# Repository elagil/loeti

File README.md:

# Löti

Soldering station hardware and firmware, powered by USB PD, delivering up to 100 W.

Supports irons with thermocouples as temperature probes, for example
- JBC C210
- JBC C245

## Resources

- [Hardware design](./hardware)
- [Firmware](./firmware)

## Updating firmware

On the device, either
- hold the `BOOT`-button on the PCB and insert the USB cable into the data/debug port, or
- go to the user menu (long-press encoder button), scroll down to `DFU mode`, and select.

Once in DFU mode, flash a binary from the release artifacts. For example with

```bash
dfu-util -a 0 -s 0x08000000:leave -D <firmware_file_name>.bin
```

## The finished product

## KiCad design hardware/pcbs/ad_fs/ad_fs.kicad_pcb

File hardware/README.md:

# Hardware design

There are three PCBs that complete the build.

- The [main PCB](pcbs/main/),
- the [REAN TinyXLR adapter board](pcbs/adapter/), and
- a [holder for the acrylic display protection glass](pcbs/holder/).

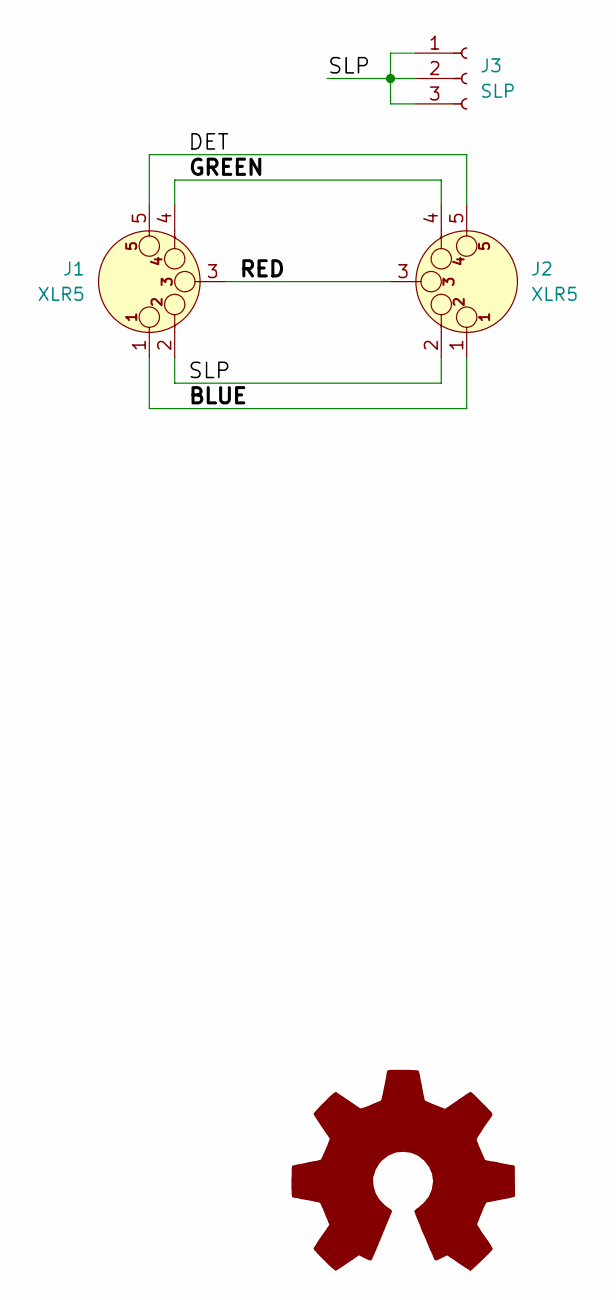
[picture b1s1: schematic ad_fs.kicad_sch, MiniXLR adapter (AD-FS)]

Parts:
J1, J2: XLR5; MiniXLR-5_Rean_RT5MPR
J3: SLP; PinSocket_1x03_P2.00mm_Vertical
oshw1: Logo_Open_Hardware_Large; OSHW-Symbol_6.7x6mm_SilkScreen

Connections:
/BLUE: J1.1, J2.1
/DET: J1.5, J2.5
/GREEN: J1.4 (P3), J2.4 (P3)
/RED: J1.3, J2.3
/SLP: J1.2, J2.2, J3.1, J3.2, J3.3

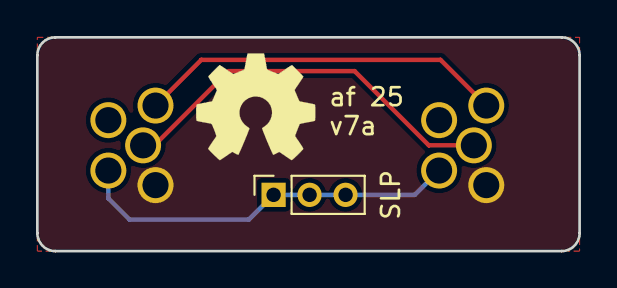
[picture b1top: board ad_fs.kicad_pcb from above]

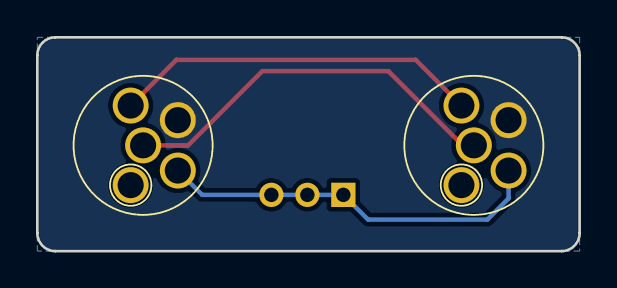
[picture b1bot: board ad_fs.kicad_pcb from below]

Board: 2 copper layers, 30.1 x 11.9 mm, 4 parts (2 on the bottom side), 5 nets.

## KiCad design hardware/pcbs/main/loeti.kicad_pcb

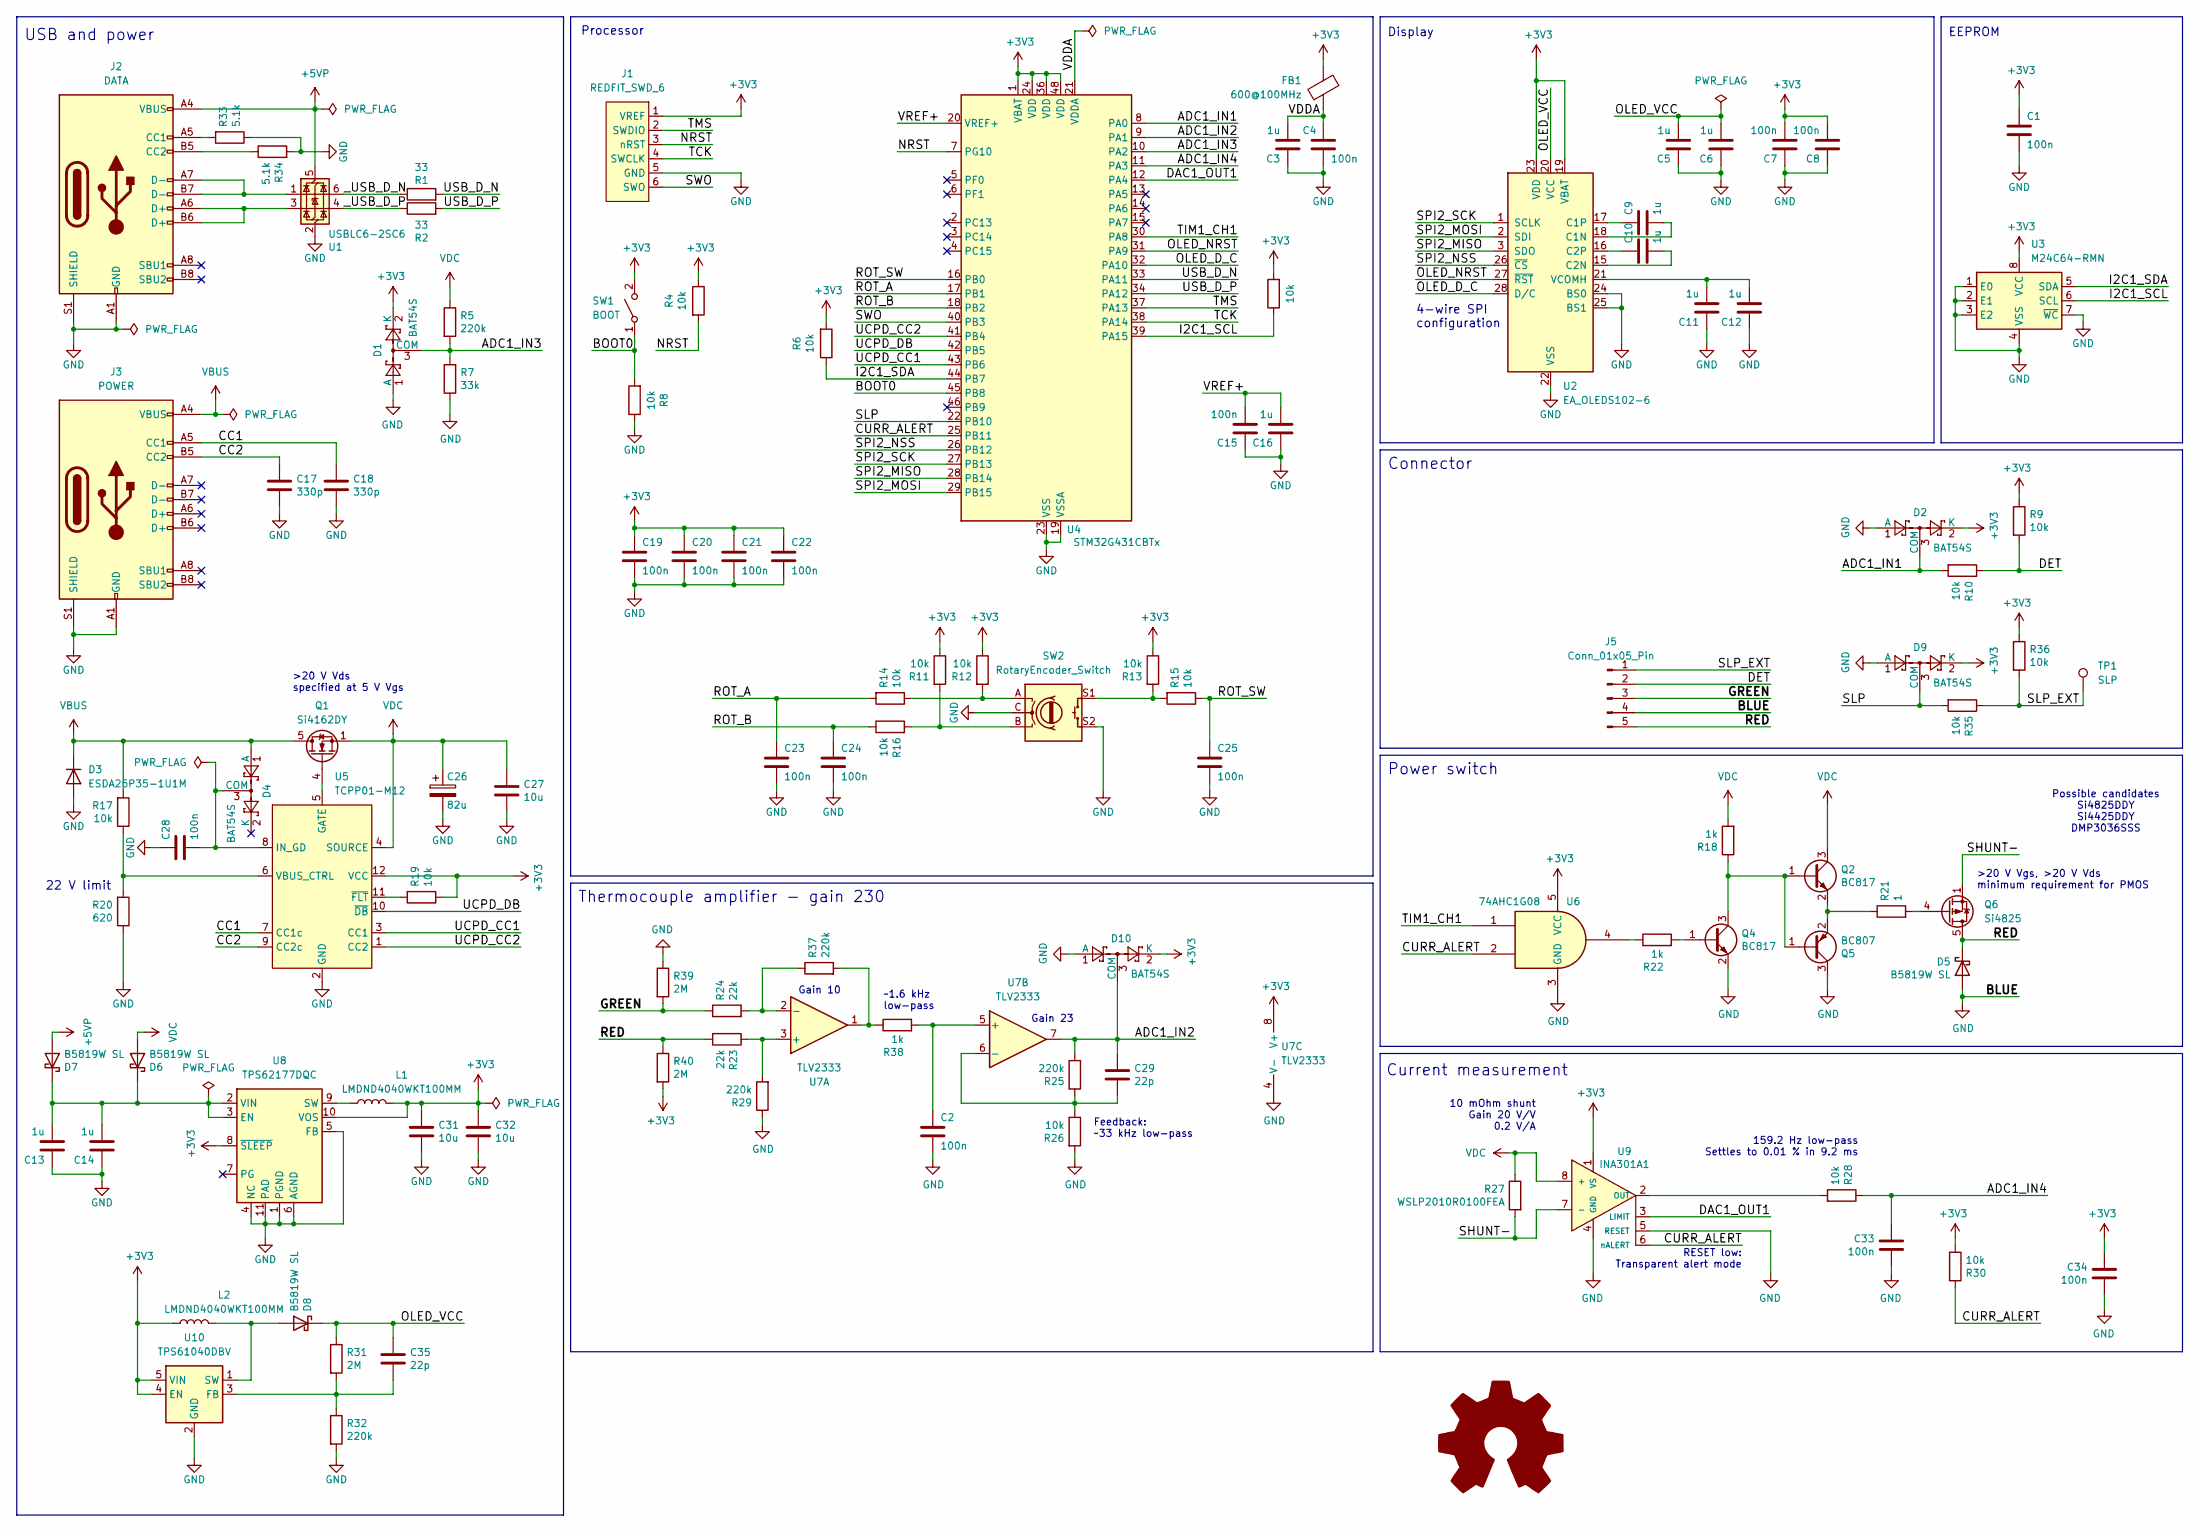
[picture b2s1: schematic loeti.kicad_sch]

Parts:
C1, C2, C4, C7, C8, C15, C19, C20, C21, C22, C23, C24, C25, C28, C33, C34: 100n; C_0603_1608Metric; MPN C14663
C3, C5, C6, C9, C10, C11, C12, C13, C14, C16: 1u; C_0603_1608Metric; MPN C15849
C17, C18: 330p; C_0603_1608Metric; MPN C1664
C26: 82u; CP_Radial_D8.0mm_P3.50mm
C27, C31, C32: 10u; C_1206_3216Metric; MPN C13585
C29, C35: 22p; C_0603_1608Metric; MPN C1653
D1, D2, D4, D9, D10: BAT54S; SOT-23; MPN C83935
D3: ESDA25P35-1U1M; ST_QFN-2L_1.6x1.0mm; MPN C1974707
D5, D6, D7, D8: B5819W SL; D_SOD-123; MPN C8598
FB1: 600@100MHz; L_0603_1608Metric; MPN C1002
J1: REDFIT_SWD_6; WR-WST REDFIT IDC 6 DBG
J2: DATA; USB_C_Receptacle_HRO_TYPE-C-31-M-12; MPN C165948
J3: POWER; USB_C_Receptacle_HRO_TYPE-C-31-M-12; MPN C165948
J5: Conn_01x05_Pin; PinHeader_1x05_P2.54mm_Horizontal
L1, L2: LMDND4040WKT100MM; L_Abracon_ASPI-0425
Q1: Si4162DY; SOIC-8_3.9x4.9mm_P1.27mm; MPN C727585
Q2, Q4: BC817; SOT-23; MPN C466643
Q5: BC807; SOT-23; MPN C466642
Q6: Si4825; SOIC-8_3.9x4.9mm_P1.27mm; MPN C3289788
R1, R2: 33; R_0603_1608Metric; MPN C23140
R3, R4, R6, R8, R9, R10, R11, R12, R13, R14, R15, R16, R17, R19, R26, R28, R30, R35, R36: 10k; R_0603_1608Metric; MPN C25804
R5, R25, R29, R32, R37: 220k; R_0603_1608Metric; MPN C22961
R7: 33k; R_0603_1608Metric; MPN C4216
R18, R22, R38: 1k; R_0603_1608Metric; MPN C21190
R20: 620; R_0603_1608Metric
R21: 1; R_0603_1608Metric; MPN C22936
R23, R24: 22k; R_0603_1608Metric; MPN C31850
R27: WSLP2010R0100FEA; R_2010_5025Metric; MPN C844087
R31, R39, R40: 2M; R_0603_1608Metric; MPN C22976
R33, R34: 5.1k; R_0603_1608Metric; MPN C23186
SW1: BOOT; SW_SPST_TL3342; MPN C318884
SW2: RotaryEncoder_Switch; RotaryEncoder_Bourns_Horizontal_PEC09-2xxxF-Sxxxx
TP1: SLP; TestPoint_Plated_Hole_D2.0mm
U1: USBLC6-2SC6; SOT-23-6; MPN C7519; JLCPCB Rotation Offset 180
U2: EA_OLEDS102-6
U3: M24C64-RMN; SOIC-8_3.9x4.9mm_P1.27mm; MPN C79988; JLCPCB Rotation Offset -90
U4: STM32G431CBTx; LQFP-48_7x7mm_P0.5mm; MPN C529355
U5: TCPP01-M12; QFN-12-1EP_3x3mm_P0.51mm_EP1.45x1.45mm; MPN C1121848
U6: 74AHC1G08; SOT-353_SC-70-5; MPN C459531
U7: TLV2333; SOIC-8_3.9x4.9mm_P1.27mm; MPN C176649
U8: TPS62177DQC; WSON-10-1EP_2x3mm_P0.5mm_EP0.84x2.4mm_ThermalVias; MPN C91241
U9: INA301A1; VSSOP-8_3x3mm_P0.65mm; MPN C471062
U10: TPS61040DBV; SOT-23-5
oshw1: Logo_Open_Hardware_Large; OSHW-Symbol_6.7x6mm_SilkScreen

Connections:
+3V3: C1.1, C7.2, C8.2, C19.1, C20.1, C21.1, C22.1, C31.1, C32.1, C34.1, D1.2 (K), D2.2 (K), D9.2 (K), D10.2 (K), FB1.1, J1.1 (VREF), L1.2, L2.1, R3.2, R4.1, R6.2, R9.1, R11.1, R12.1, R13.1, R19.1, R30.2, R36.1, R40.2, SW1.2 (B), U2.19 (VBAT), U2.23 (VDD), U3.8 (VCC), U4.1 (VBAT), U4.24 (VDD), U4.36 (VDD), U4.48 (VDD), U5.12 (VCC), U6.5 (VCC), U7.8 (V+), U8.8 (~SLEEP), U8.10 (VOS), U9.1 (VS), U10.4 (EN), U10.5 (VIN)
+5VP: D7.2 (A), J2.A4 (VBUS), J2.A9 (VBUS), J2.B4 (VBUS), J2.B9 (VBUS), U1.5 (VBUS)
/ADC1_IN1: D2.3 (COM), R10.2, U4.8 (PA0)
/ADC1_IN2: C29.1, D10.3 (COM), R25.2, U4.9 (PA1), U7.7
/ADC1_IN3: D1.3 (COM), R5.2, R7.2, U4.10 (PA2)
/ADC1_IN4: C33.1, R28.1, U4.11 (PA3)
/BOOT0: R8.2, SW1.1 (A), U4.45 (PB8)
/CC1: C18.1, J3.A5 (CC1), U5.7 (CC1c)
/CC2: C17.1, J3.B5 (CC2), U5.9 (CC2c)
/CURR_ALERT: R30.1, U4.25 (PB11), U6.2, U9.6 (nALERT)
/DAC1_OUT1: U4.12 (PA4), U9.3 (LIMIT)
/DET: J5.2, R9.2, R10.1
/GREEN: J5.3, R24.1, R39.2
/I2C1_SCL: R3.1, U3.6 (SCL), U4.39 (PA15)
/I2C1_SDA: R6.1, U3.5 (SDA), U4.44 (PB7)
/NRST: J1.3 (nRST), R4.2, U4.7 (PG10)
/OLED_D_C: U2.28 (D/C), U4.32 (PA10)
/OLED_NRST: U2.27 (~RST), U4.31 (PA9)
/OLED_VCC: C5.2, C6.2, C35.1, D8.1 (K), R31.1, U2.20 (VCC)
/RED: D5.1 (K), J5.5, Q6.5 (D), Q6.6 (D), Q6.7 (D), Q6.8 (D), R23.2, R40.1
/ROT_A: C23.1, R14.2, U4.17 (PB1)
/ROT_B: C24.1, R16.1, U4.18 (PB2)
/ROT_SW: C25.1, R15.1, U4.16 (PB0)
/SHUNT-: Q6.1 (S), Q6.2 (S), Q6.3 (S), R27.2, U9.7 (-)
/SLP: D9.3 (COM), R35.2, U4.22 (PB10)
/SLP_EXT: J5.1, R35.1, R36.2, TP1.1
/SPI2_MISO: U2.3 (SDO), U4.28 (PB14)
/SPI2_MOSI: U2.2 (SDI), U4.29 (PB15)
/SPI2_NSS: U2.26 (~CS), U4.26 (PB12)
/SPI2_SCK: U2.1 (SCLK), U4.27 (PB13)
/SWO: J1.6 (SWO), U4.40 (PB3)
/TCK: J1.4 (SWCLK), U4.38 (PA14)
/TIM1_CH1: U4.30 (PA8), U6.1
/TMS: J1.2 (SWDIO), U4.37 (PA13)
/UCPD_CC1: U4.43 (PB6), U5.3 (CC1)
/UCPD_CC2: U4.41 (PB4), U5.1 (CC2)
/UCPD_DB: U4.42 (PB5), U5.10 (~DB)
/USB_D_N: R1.2, U4.33 (PA11)
/USB_D_P: R2.2, U4.34 (PA12)
/VDDA: C3.2, C4.1, FB1.2, U4.21 (VDDA)
/VREF+: C15.2, C16.2, U4.20 (VREF+)
/_USB_D_N: R1.1, U1.6 (I/O1)
/_USB_D_P: R2.1, U1.4 (I/O2)
GND: C1.2, C2.2, C3.1, C4.2, C5.1, C6.1, C7.1, C8.1, C11.1, C12.1, C13.1, C14.1, C15.1, C16.1, C17.2, C18.2, C19.2, C20.2, C21.2, C22.2, C23.2, C24.2, C25.2, C26.2, C27.2, C28.1, C31.2, C32.2, C33.2, C34.2, D1.1 (A), D2.1 (A), D3.2 (A), D5.2 (A), D9.1 (A), D10.1 (A), J1.5 (GND), J2.A1 (GND), J2.A12 (GND), J2.B1 (GND), J2.B12 (GND), J2.S1 (SHIELD), J3.A1 (GND), J3.A12 (GND), J3.B1 (GND), J3.B12 (GND), J3.S1 (SHIELD), J5.4, Q4.2 (E), Q5.3 (C), R7.1, R8.1, R20.1, R26.2, R29.1, R32.2, R33.1, R34.2, R39.1, SW2.C, SW2.S2, U1.2 (GND), U2.22 (VSS), U2.24 (BS0), U2.25 (BS1), U3.1 (E0), U3.2 (E1), U3.3 (E2), U3.4 (VSS), U3.7 (~WC), U4.19 (VSSA), U4.23 (VSS), U4.35 (VSS), U4.47 (VSS), U5.2 (GND), U5.13 (GND), U6.3 (GND), U7.4 (V-), U8.1 (PGND), U8.4 (NC), U8.5 (FB), U8.6 (AGND), U8.11 (PAD), U9.4 (GND), U9.5 (RESET), U10.2 (GND)
unnamed: C28.2, D4.3 (COM), U5.8 (IN_GD)
unnamed: C13.2, C14.2, D6.1 (K), D7.1 (K), U8.2 (VIN), U8.3 (EN)
unnamed: D8.2 (A), L2.2, U10.1 (SW)
unnamed: J2.A5 (CC1), R33.2
unnamed: J2.B5 (CC2), R34.1
unnamed: J2.A6 (D+), J2.B6 (D+), U1.3 (I/O2)
unnamed: J2.A7 (D-), J2.B7 (D-), U1.1 (I/O1)
unnamed: Q1.4 (G), U5.5 (GATE)
unnamed: Q2.1 (B), Q4.3 (C), Q5.1 (B), R18.1
unnamed: Q2.2 (E), Q5.2 (E), R21.1
unnamed: Q4.1 (B), R22.2
unnamed: Q6.4 (G), R21.2
unnamed: R11.2, R16.2, SW2.B
unnamed: R12.2, R14.1, SW2.A
unnamed: R13.2, R15.2, SW2.S1
unnamed: R22.1, U6.4
unnamed: R37.2, R38.1, U7.1
unnamed: C9.2, U2.18 (C1N)
unnamed: C9.1, U2.17 (C1P)
unnamed: C10.2, U2.15 (C2N)
unnamed: C10.1, U2.16 (C2P)
unnamed: C11.2, C12.2, U2.21 (VCOMH)
unnamed: R17.1, R20.2, U5.6 (VBUS_CTRL)
unnamed: R19.2, U5.11 (~FLT)
unnamed: R23.1, R29.2, U7.3 (+)
unnamed: R24.2, R37.1, U7.2 (-)
unnamed: C2.1, R38.2, U7.5 (+)
unnamed: C29.2, R25.1, R26.1, U7.6 (-)
unnamed: L1.1, U8.9 (SW)
unnamed: R28.2, U9.2 (OUT)
unnamed: C35.2, R31.2, R32.1, U10.3 (FB)
VBUS: D3.1 (K), D4.1 (A), J3.A4 (VBUS), J3.A9 (VBUS), J3.B4 (VBUS), J3.B9 (VBUS), Q1.5 (D), Q1.6 (D), Q1.7 (D), Q1.8 (D), R17.2
VDC: C26.1, C27.1, D6.2 (A), Q1.1 (S), Q1.2 (S), Q1.3 (S), Q2.3 (C), R5.1, R18.2, R27.1, U5.4 (SOURCE), U9.8 (+)

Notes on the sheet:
~1.6 kHz low-pass
>20 V Vgs, >20 V Vds minimum requirement for PMOS
USB and power
22 V limit
>20 V Vds specified at 5 V Vgs
159.2 Hz low-pass Settles to 0.01 % in 9.2 ms
RESET low: Transparent alert mode
Connector
EEPROM
Possible candidates Si4825DDY Si4425DDY DMP3036SSS
Gain 23
Gain 10
Feedback: ~33 kHz low-pass
Thermocouple amplifier - gain 230
Power switch
4-wire SPI configuration
Display
Processor
10 mOhm shunt Gain 20 V/V 0.2 V/A
Current measurement

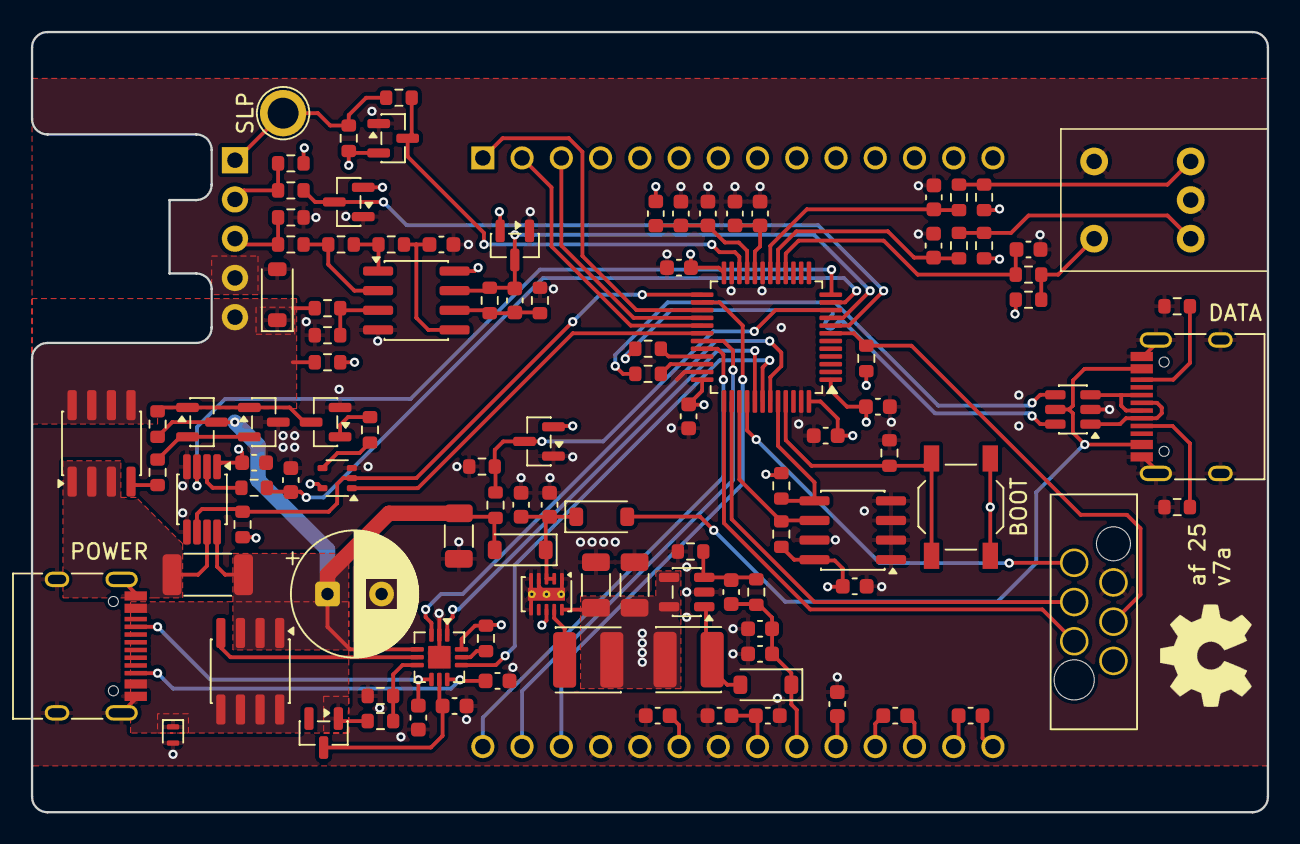
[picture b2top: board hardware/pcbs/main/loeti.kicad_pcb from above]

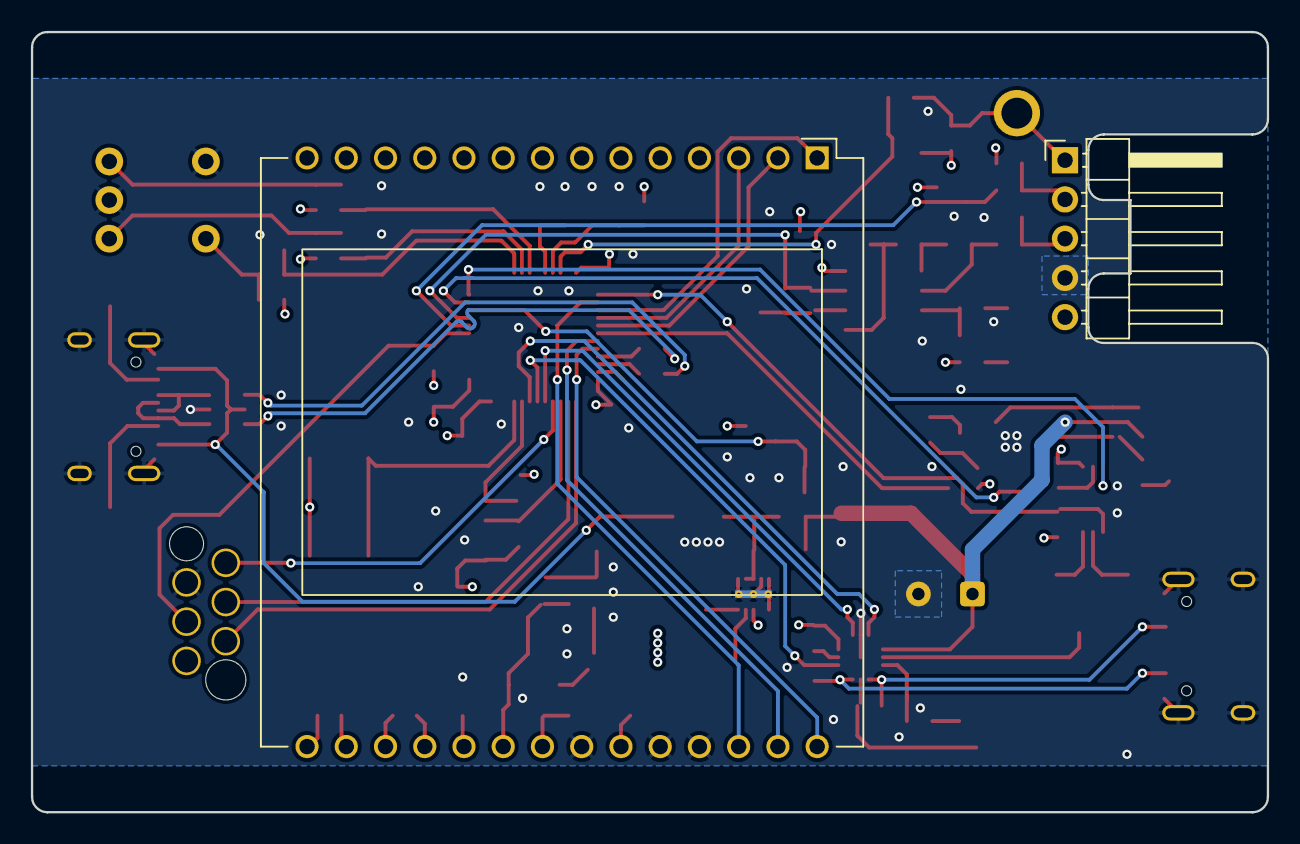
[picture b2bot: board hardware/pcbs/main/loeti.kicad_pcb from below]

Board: 4 copper layers, 80.0 x 50.5 mm, 110 parts (2 on the bottom side), 77 nets.

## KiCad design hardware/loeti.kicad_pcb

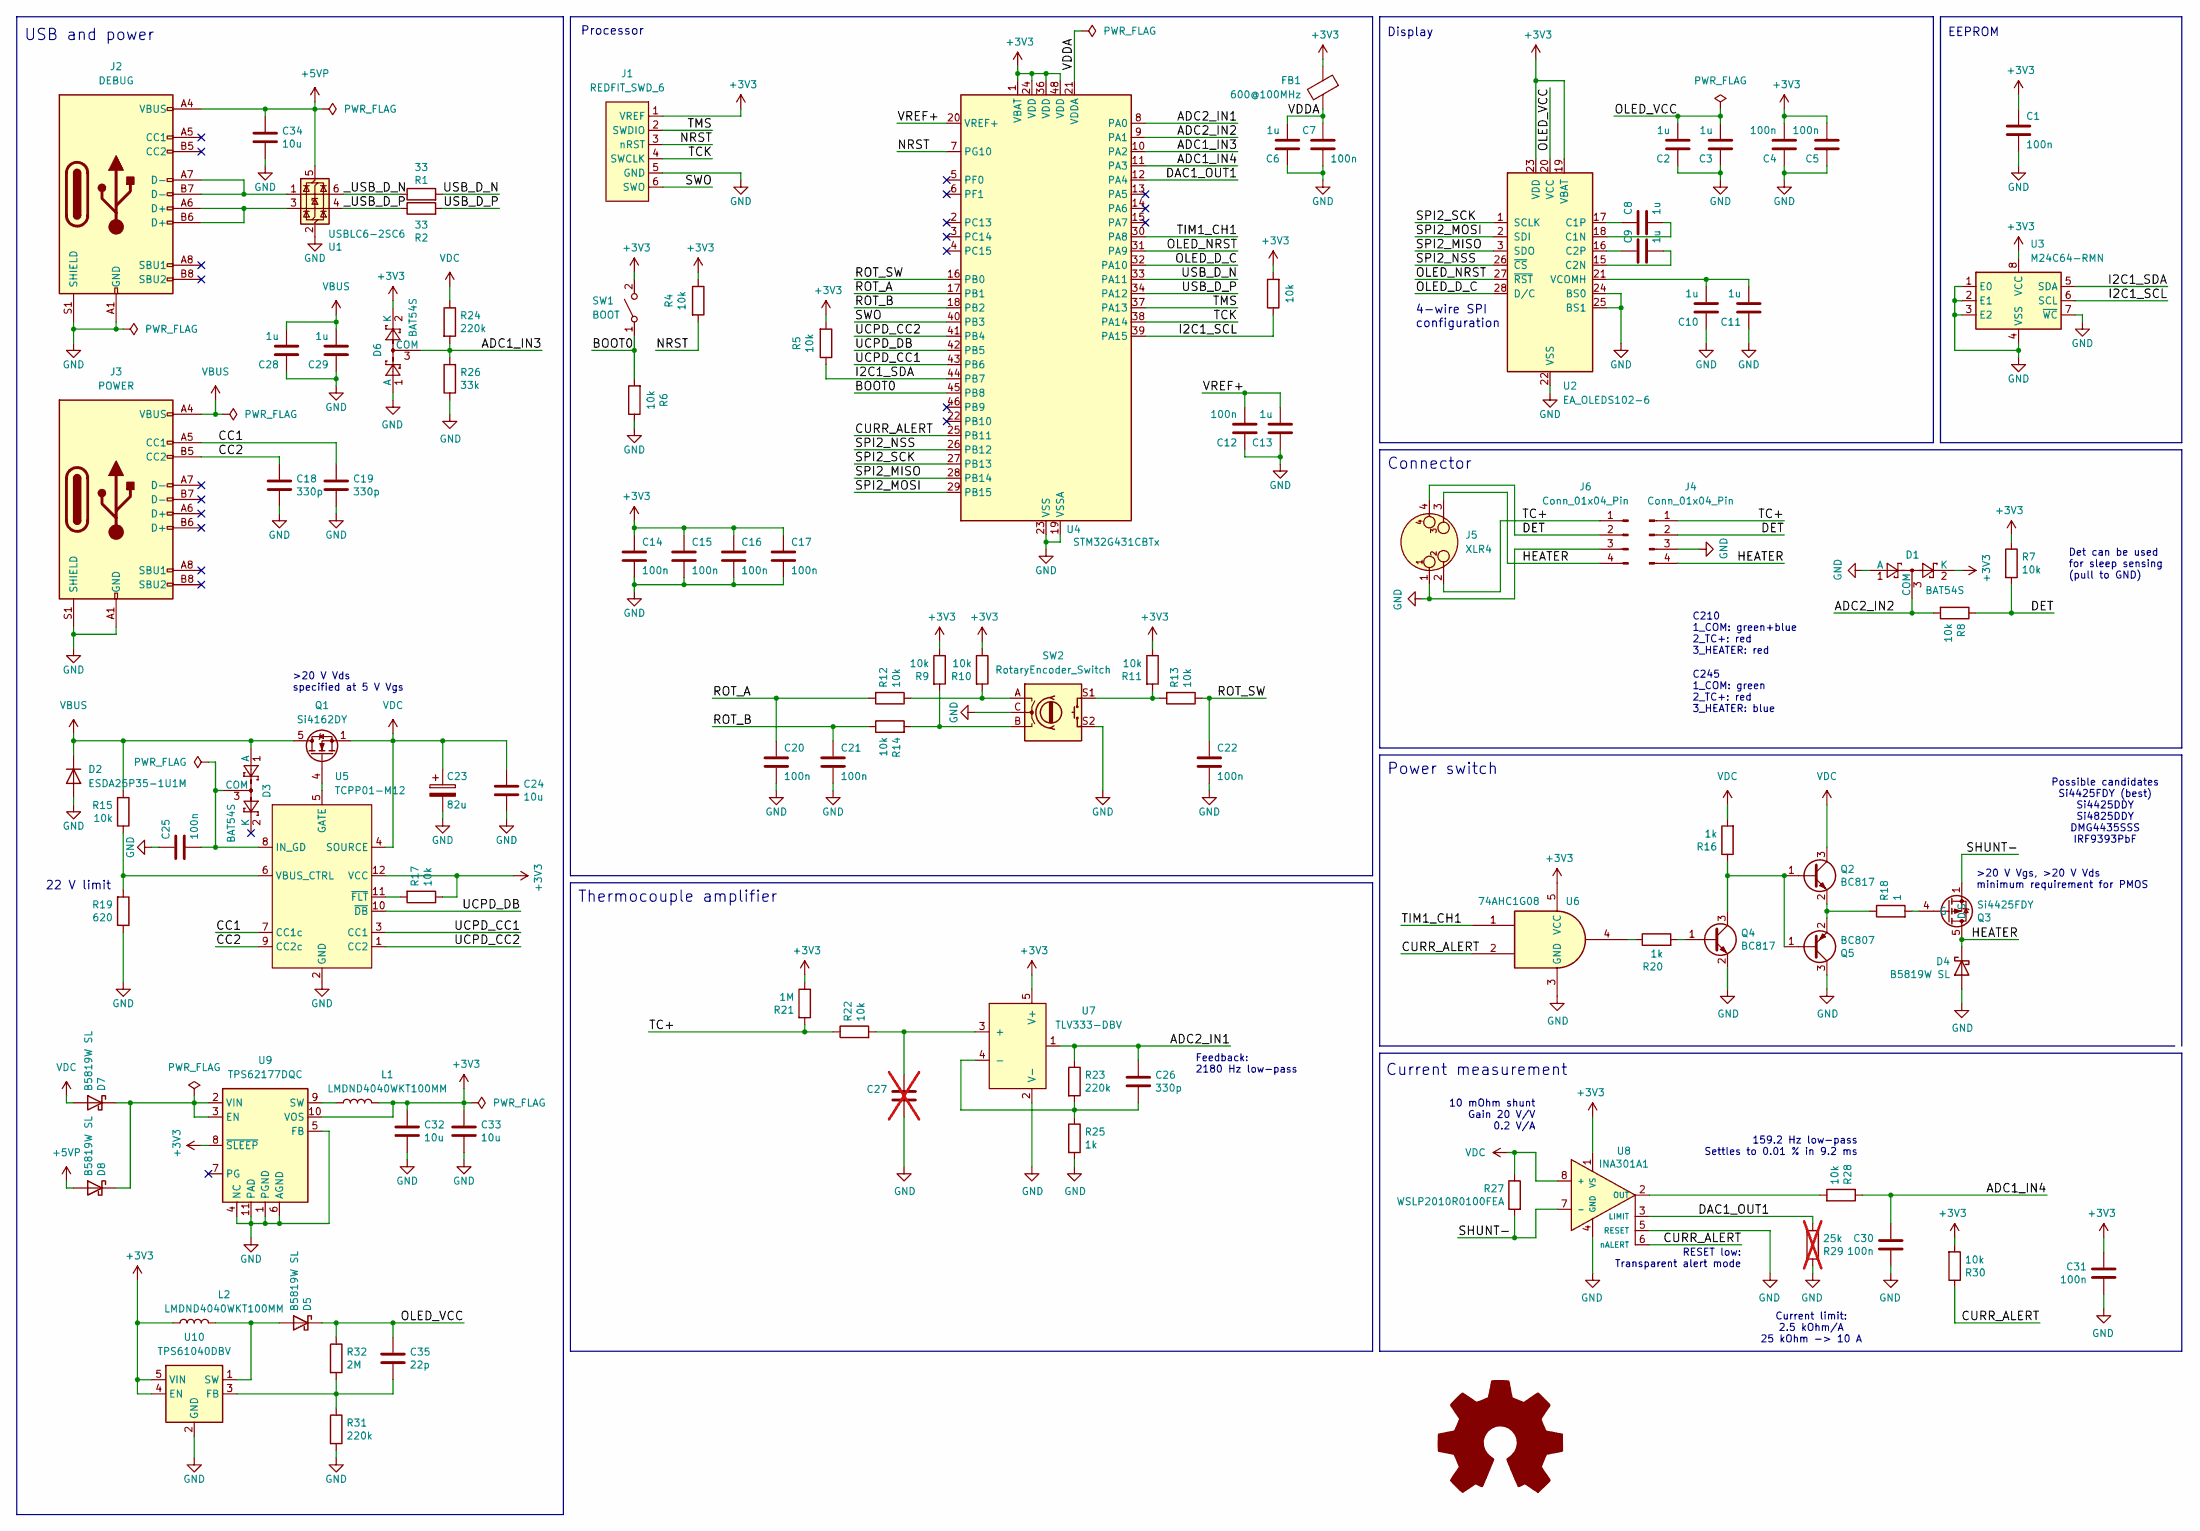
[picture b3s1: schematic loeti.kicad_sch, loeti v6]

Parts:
C1, C4, C5, C7, C12, C14, C15, C16, C17, C20, C21, C22, C25, C30, C31: 100n; C_0603_1608Metric; MPN C14663
C2, C3, C6, C8, C9, C10, C11, C13, C28, C29: 1u; C_0603_1608Metric; MPN C15849
C18, C19, C26: 330p; C_0603_1608Metric; MPN C1664
C23: 82u; CP_Radial_D10.0mm_P3.50mm
C24, C32, C33, C34: 10u; C_1206_3216Metric; MPN C13585
C27: C_0603_1608Metric; not fitted
C35: 22p; C_0603_1608Metric; MPN C1664
D1, D3, D6: BAT54S; SOT-23; MPN C83935
D2: ESDA25P35-1U1M; ST_QFN-2L_1.6x1.0mm; MPN C1974707
D4, D5, D7, D8: B5819W SL; D_SOD-123; MPN C8598
FB1: 600@100MHz; L_0603_1608Metric; MPN C1002
J1: REDFIT_SWD_6; WR-WST REDFIT IDC 6 DBG
J2: DEBUG; USB_C_Receptacle_HRO_TYPE-C-31-M-12; MPN C165948
J3: POWER; USB_C_Receptacle_HRO_TYPE-C-31-M-12; MPN C165948
J4: Conn_01x04_Pin; PinHeader_1x04_P2.54mm_Horizontal
J5: XLR4; MiniXLR-4_Rean_RT4MPR
J6: Conn_01x04_Pin; PinHeader_1x04_P2.54mm_Vertical
L1, L2: LMDND4040WKT100MM; L_Abracon_ASPI-0425
Q1: Si4162DY; SOIC-8_3.9x4.9mm_P1.27mm; MPN C727585
Q2, Q4: BC817; SOT-23; MPN C466643
Q3: Si4425FDY; SO-8_3.9x4.9mm_P1.27mm; MPN C3289788
Q5: BC807; SOT-23; MPN C466642
R1, R2: 33; R_0603_1608Metric; MPN C23140
R3, R4, R5, R6, R7, R8, R9, R10, R11, R12, R13, R14, R15, R17, R22, R28, R30: 10k; R_0603_1608Metric; MPN C25804
R16, R20, R25: 1k; R_0603_1608Metric; MPN C21190
R18: 1; R_0603_1608Metric; MPN C22936
R19: 620; R_0603_1608Metric
R21: 1M; R_0603_1608Metric; MPN C22935
R23, R24, R31: 220k; R_0603_1608Metric; MPN C22961
R26: 33k; R_0603_1608Metric; MPN C4216
R27: WSLP2010R0100FEA; R_2010_5025Metric; MPN C844087
R29: 25k; R_0603_1608Metric; not fitted
R32: 2M; R_0603_1608Metric; MPN C22961
SW1: BOOT; SW_SPST_TL3342; MPN C318884
SW2: RotaryEncoder_Switch; RotaryEncoder_Bourns_Horizontal_PEC09-2xxxF-Sxxxx
U1: USBLC6-2SC6; SOT-23-6; MPN C7519; JLCPCB Rotation Offset 180
U2: EA_OLEDS102-6
U3: M24C64-RMN; SOIC-8_3.9x4.9mm_P1.27mm; MPN C79988; JLCPCB Rotation Offset -90
U4: STM32G431CBTx; LQFP-48_7x7mm_P0.5mm; MPN C529355
U5: TCPP01-M12; QFN-12-1EP_3x3mm_P0.51mm_EP1.45x1.45mm; MPN C1121848
U6: 74AHC1G08; SOT-353_SC-70-5; MPN C459531
U7: TLV333-DBV; SOT-23-5; MPN C75209
U8: INA301A1; VSSOP-8_3x3mm_P0.65mm; MPN C471062
U9: TPS62177DQC; WSON-10-1EP_2x3mm_P0.5mm_EP0.84x2.4mm_ThermalVias; MPN C91241
U10: TPS61040DBV; SOT-23-5
oshw1: Logo_Open_Hardware_Large; OSHW-Symbol_6.7x6mm_SilkScreen

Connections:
+3V3: C1.1, C4.2, C5.2, C14.1, C15.1, C16.1, C17.1, C31.1, C32.1, C33.1, D1.2 (K), D6.2 (K), FB1.1, J1.1 (VREF), L1.2, L2.1, R3.2, R4.1, R5.2, R7.1, R9.1, R10.1, R11.1, R17.1, R21.1, R30.2, SW1.2 (B), U2.19 (VBAT), U2.23 (VDD), U3.8 (VCC), U4.1 (VBAT), U4.24 (VDD), U4.36 (VDD), U4.48 (VDD), U5.12 (VCC), U6.5 (VCC), U7.5 (V+), U8.1 (VS), U9.8 (~SLEEP), U9.10 (VOS), U10.4 (EN), U10.5 (VIN)
+5VP: C34.1, D8.2 (A), J2.A4 (VBUS), J2.A9 (VBUS), J2.B4 (VBUS), J2.B9 (VBUS), U1.5 (VBUS)
/ADC1_IN3: D6.3 (COM), R24.2, R26.2, U4.10 (PA2)
/ADC1_IN4: C30.1, R28.1, U4.11 (PA3)
/ADC2_IN1: C26.1, R23.1, U4.8 (PA0), U7.1
/ADC2_IN2: D1.3 (COM), R8.2, U4.9 (PA1)
/BOOT0: R6.2, SW1.1 (A), U4.45 (PB8)
/CC1: C19.1, J3.A5 (CC1), U5.7 (CC1c)
/CC2: C18.1, J3.B5 (CC2), U5.9 (CC2c)
/CURR_ALERT: R30.1, U4.25 (PB11), U6.2, U8.6 (nALERT)
/DAC1_OUT1: R29.2, U4.12 (PA4), U8.3 (LIMIT)
/DET: J4.2, J5.4, J6.2, R7.2, R8.1
/HEATER: D4.1 (K), J4.4, J5.3, J6.4, Q3.5 (D), Q3.6 (D), Q3.7 (D), Q3.8 (D)
/I2C1_SCL: R3.1, U3.6 (SCL), U4.39 (PA15)
/I2C1_SDA: R5.1, U3.5 (SDA), U4.44 (PB7)
/NRST: J1.3 (nRST), R4.2, U4.7 (PG10)
/OLED_D_C: U2.28 (D/C), U4.32 (PA10)
/OLED_NRST: U2.27 (~RST), U4.31 (PA9)
/OLED_VCC: C2.2, C3.2, C35.1, D5.1 (K), R32.1, U2.20 (VCC)
/ROT_A: C20.1, R12.2, U4.17 (PB1)
/ROT_B: C21.1, R14.1, U4.18 (PB2)
/ROT_SW: C22.1, R13.1, U4.16 (PB0)
/SHUNT-: Q3.1 (S), Q3.2 (S), Q3.3 (S), R27.2, U8.7 (-)
/SPI2_MISO: U2.3 (SDO), U4.28 (PB14)
/SPI2_MOSI: U2.2 (SDI), U4.29 (PB15)
/SPI2_NSS: U2.26 (~CS), U4.26 (PB12)
/SPI2_SCK: U2.1 (SCLK), U4.27 (PB13)
/SWO: J1.6 (SWO), U4.40 (PB3)
/TC+: J4.1, J5.2, J6.1, R21.2, R22.1
/TCK: J1.4 (SWCLK), U4.38 (PA14)
/TIM1_CH1: U4.30 (PA8), U6.1
/TMS: J1.2 (SWDIO), U4.37 (PA13)
/UCPD_CC1: U4.43 (PB6), U5.3 (CC1)
/UCPD_CC2: U4.41 (PB4), U5.1 (CC2)
/UCPD_DB: U4.42 (PB5), U5.10 (~DB)
/USB_D_N: R1.2, U4.33 (PA11)
/USB_D_P: R2.2, U4.34 (PA12)
/VDDA: C6.2, C7.1, FB1.2, U4.21 (VDDA)
/VREF+: C12.2, C13.2, U4.20 (VREF+)
/_USB_D_N: R1.1, U1.6 (I/O1)
/_USB_D_P: R2.1, U1.4 (I/O2)
GND: C1.2, C2.1, C3.1, C4.1, C5.1, C6.1, C7.2, C10.1, C11.1, C12.1, C13.1, C14.2, C15.2, C16.2, C17.2, C18.2, C19.2, C20.2, C21.2, C22.2, C23.2, C24.2, C25.1, C27.2, C28.1, C29.1, C30.2, C31.2, C32.2, C33.2, C34.2, D1.1 (A), D2.2 (A), D4.2 (A), D6.1 (A), J1.5 (GND), J2.A1 (GND), J2.A12 (GND), J2.B1 (GND), J2.B12 (GND), J2.S1 (SHIELD), J3.A1 (GND), J3.A12 (GND), J3.B1 (GND), J3.B12 (GND), J3.S1 (SHIELD), J4.3, J5.1, J6.3, Q4.2 (E), Q5.3 (C), R6.1, R19.1, R25.2, R26.1, R29.1, R31.2, SW2.C, SW2.S2, U1.2 (GND), U2.22 (VSS), U2.24 (BS0), U2.25 (BS1), U3.1 (E0), U3.2 (E1), U3.3 (E2), U3.4 (VSS), U3.7 (~WC), U4.19 (VSSA), U4.23 (VSS), U4.35 (VSS), U4.47 (VSS), U5.2 (GND), U5.13 (GND), U6.3 (GND), U7.2 (V-), U8.4 (GND), U8.5 (RESET), U9.1 (PGND), U9.4 (NC), U9.5 (FB), U9.6 (AGND), U9.11 (PAD), U10.2 (GND)
unnamed: C25.2, D3.3 (COM), U5.8 (IN_GD)
unnamed: D5.2 (A), L2.2, U10.1 (SW)
unnamed: D7.1 (K), D8.1 (K), U9.2 (VIN), U9.3 (EN)
unnamed: J2.A6 (D+), J2.B6 (D+), U1.3 (I/O2)
unnamed: J2.A7 (D-), J2.B7 (D-), U1.1 (I/O1)
unnamed: Q1.4 (G), U5.5 (GATE)
unnamed: Q2.1 (B), Q4.3 (C), Q5.1 (B), R16.1
unnamed: Q2.2 (E), Q5.2 (E), R18.1
unnamed: Q3.4 (G), R18.2
unnamed: Q4.1 (B), R20.2
unnamed: R10.2, R12.1, SW2.A
unnamed: R11.2, R13.2, SW2.S1
unnamed: R9.2, R14.2, SW2.B
unnamed: R20.1, U6.4
unnamed: C8.2, U2.18 (C1N)
unnamed: C8.1, U2.17 (C1P)
unnamed: C9.2, U2.15 (C2N)
unnamed: C9.1, U2.16 (C2P)
unnamed: C10.2, C11.2, U2.21 (VCOMH)
unnamed: R15.1, R19.2, U5.6 (VBUS_CTRL)
unnamed: R17.2, U5.11 (~FLT)
unnamed: C27.1, R22.2, U7.3 (+)
unnamed: C26.2, R23.2, R25.1, U7.4 (-)
unnamed: R28.2, U8.2 (OUT)
unnamed: L1.1, U9.9 (SW)
unnamed: C35.2, R31.1, R32.2, U10.3 (FB)
VBUS: C28.2, C29.2, D2.1 (K), D3.1 (A), J3.A4 (VBUS), J3.A9 (VBUS), J3.B4 (VBUS), J3.B9 (VBUS), Q1.5 (D), Q1.6 (D), Q1.7 (D), Q1.8 (D), R15.2
VDC: C23.1, C24.1, D7.2 (A), Q1.1 (S), Q1.2 (S), Q1.3 (S), Q2.3 (C), R16.2, R24.1, R27.1, U5.4 (SOURCE), U8.8 (+)

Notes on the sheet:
Current limit: 2.5 kOhm/A 25 kOhm -> 10 A
>20 V Vgs, >20 V Vds minimum requirement for PMOS
C245 1_COM: green 2_TC+: red 3_HEATER: blue
USB and power
22 V limit
>20 V Vds specified at 5 V Vgs
159.2 Hz low-pass Settles to 0.01 % in 9.2 ms
RESET low: Transparent alert mode
Connector
EEPROM
Possible candidates Si4425FDY (best) Si4425DDY Si4825DDY DMG4435SSS IRF9393PbF
Feedback: 2180 Hz low-pass
Thermocouple amplifier
Det can be used for sleep sensing (pull to GND)
C210 1_COM: green+blue 2_TC+: red 3_HEATER: red
Power switch
4-wire SPI configuration
Display
Processor
10 mOhm shunt Gain 20 V/V 0.2 V/A
Current measurement

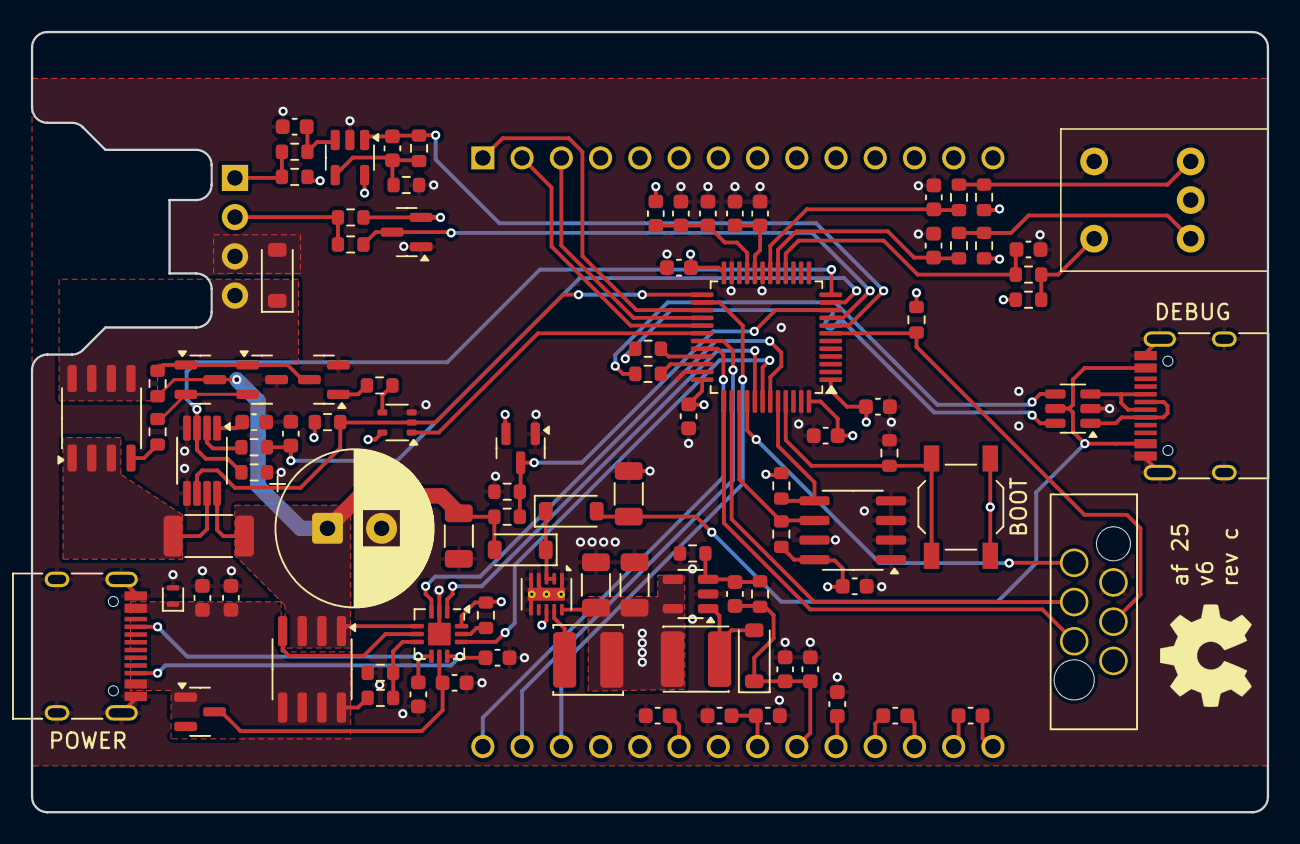
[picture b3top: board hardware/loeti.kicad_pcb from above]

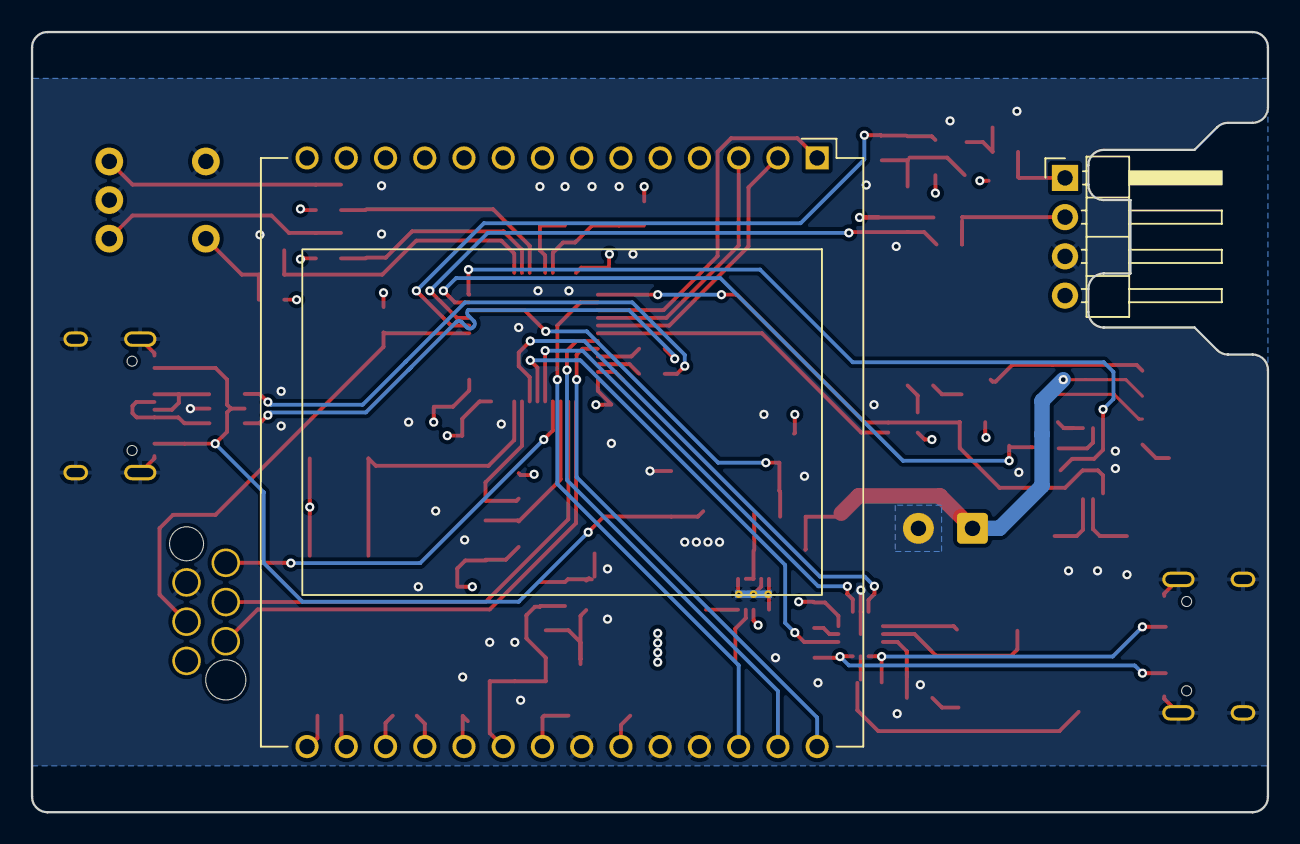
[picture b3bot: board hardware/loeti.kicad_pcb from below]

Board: 4 copper layers, 80.0 x 50.5 mm, 100 parts (2 on the bottom side), 70 nets.
